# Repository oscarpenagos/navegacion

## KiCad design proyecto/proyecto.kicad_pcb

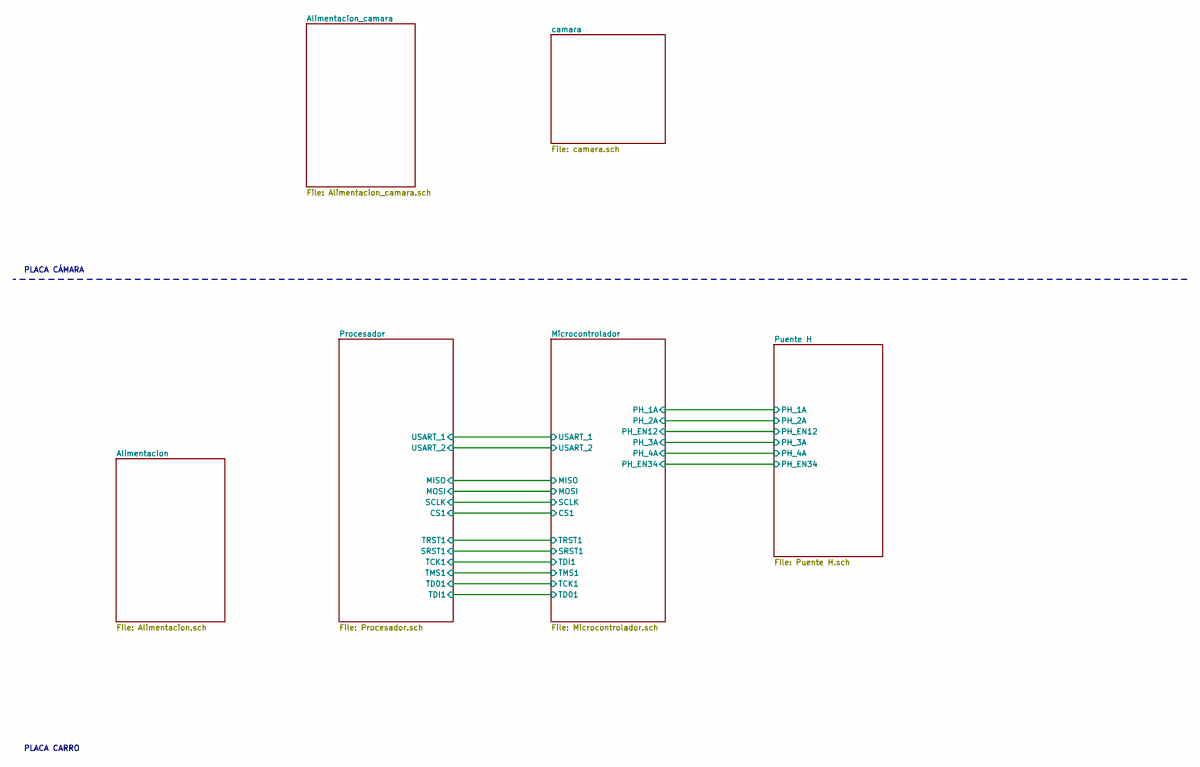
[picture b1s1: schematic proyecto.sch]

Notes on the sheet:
PLACA CÁMARA
PLACA CARRO

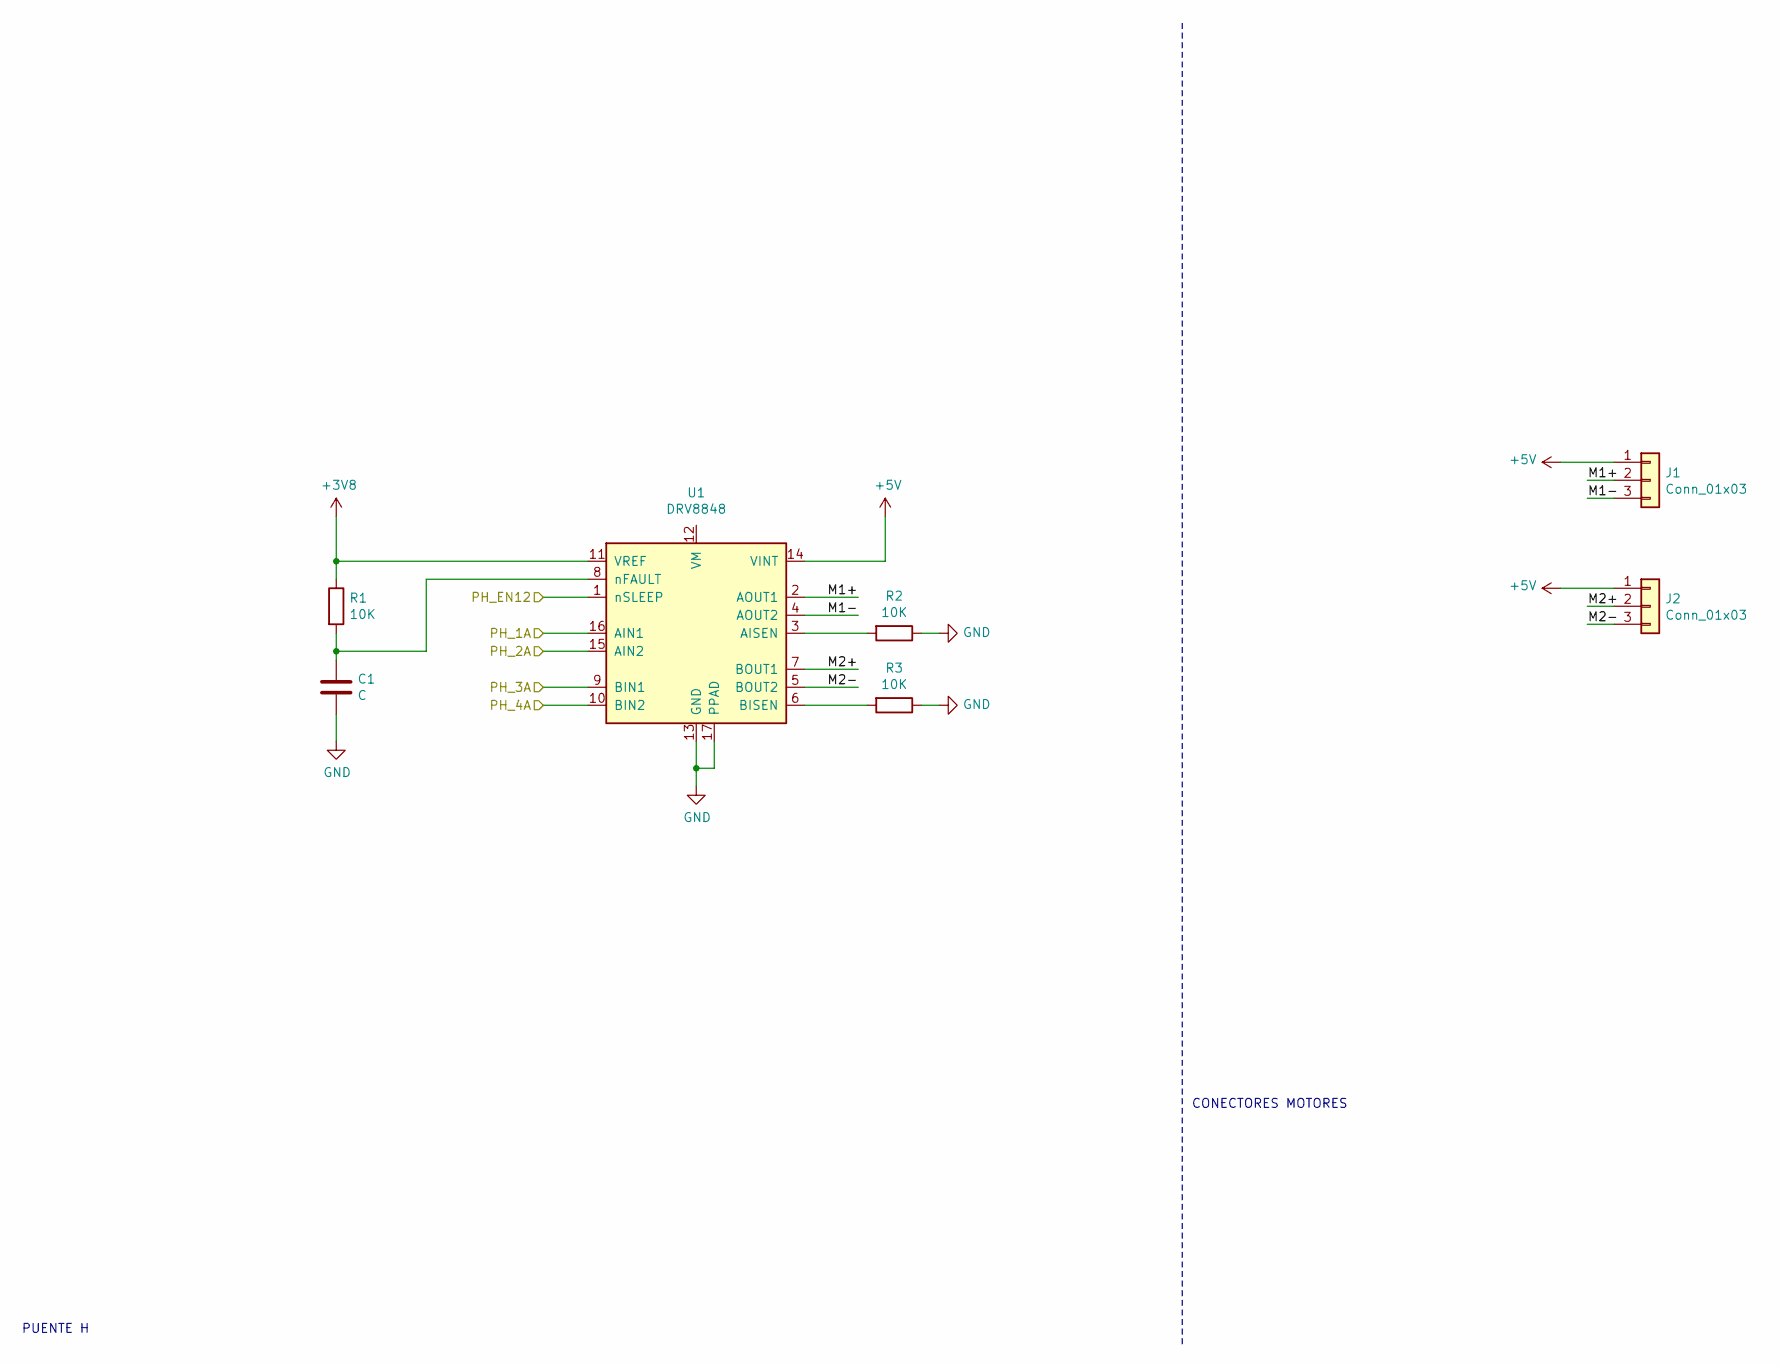
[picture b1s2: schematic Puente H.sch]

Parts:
C1: C; C_0603_1608Metric_Pad1.05x0.95mm_HandSolder
J1, J2: Conn_01x03; JST_EH_B3B-EH-A_1x03_P2.50mm_Vertical
R1, R2, R3: 10K; R_0201_0603Metric
U1: DRV8848; TSSOP-16-1EP_4.4x5mm_P0.65mm

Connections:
+3V8: R1.1, U1.11 (VREF); also elsewhere on the board
+5V: J1.1, J2.1, U1.14 (VINT); also elsewhere on the board
/Microcontrolador/PH_1A: U1.16 (AIN1); also elsewhere on the board
/Microcontrolador/PH_2A: U1.15 (AIN2); also elsewhere on the board
/Microcontrolador/PH_3A: U1.9 (BIN1); also elsewhere on the board
/Microcontrolador/PH_4A: U1.10 (BIN2); also elsewhere on the board
/Microcontrolador/PH_EN12: U1.1 (nSLEEP); also elsewhere on the board
/Puente H/M1+: J1.2, U1.2 (AOUT1)
/Puente H/M1-: J1.3, U1.4 (AOUT2)
/Puente H/M2+: J2.2, U1.7 (BOUT1)
/Puente H/M2-: J2.3, U1.5 (BOUT2)
GND: C1.2, R2.1, R3.1, U1.13 (GND), U1.17 (PPAD); also elsewhere on the board
unnamed: C1.1, R1.2, U1.8 (nFAULT)
unnamed: R2.2, U1.3 (AISEN)
unnamed: R3.2, U1.6 (BISEN)

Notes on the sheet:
CONECTORES MOTORES
PUENTE H

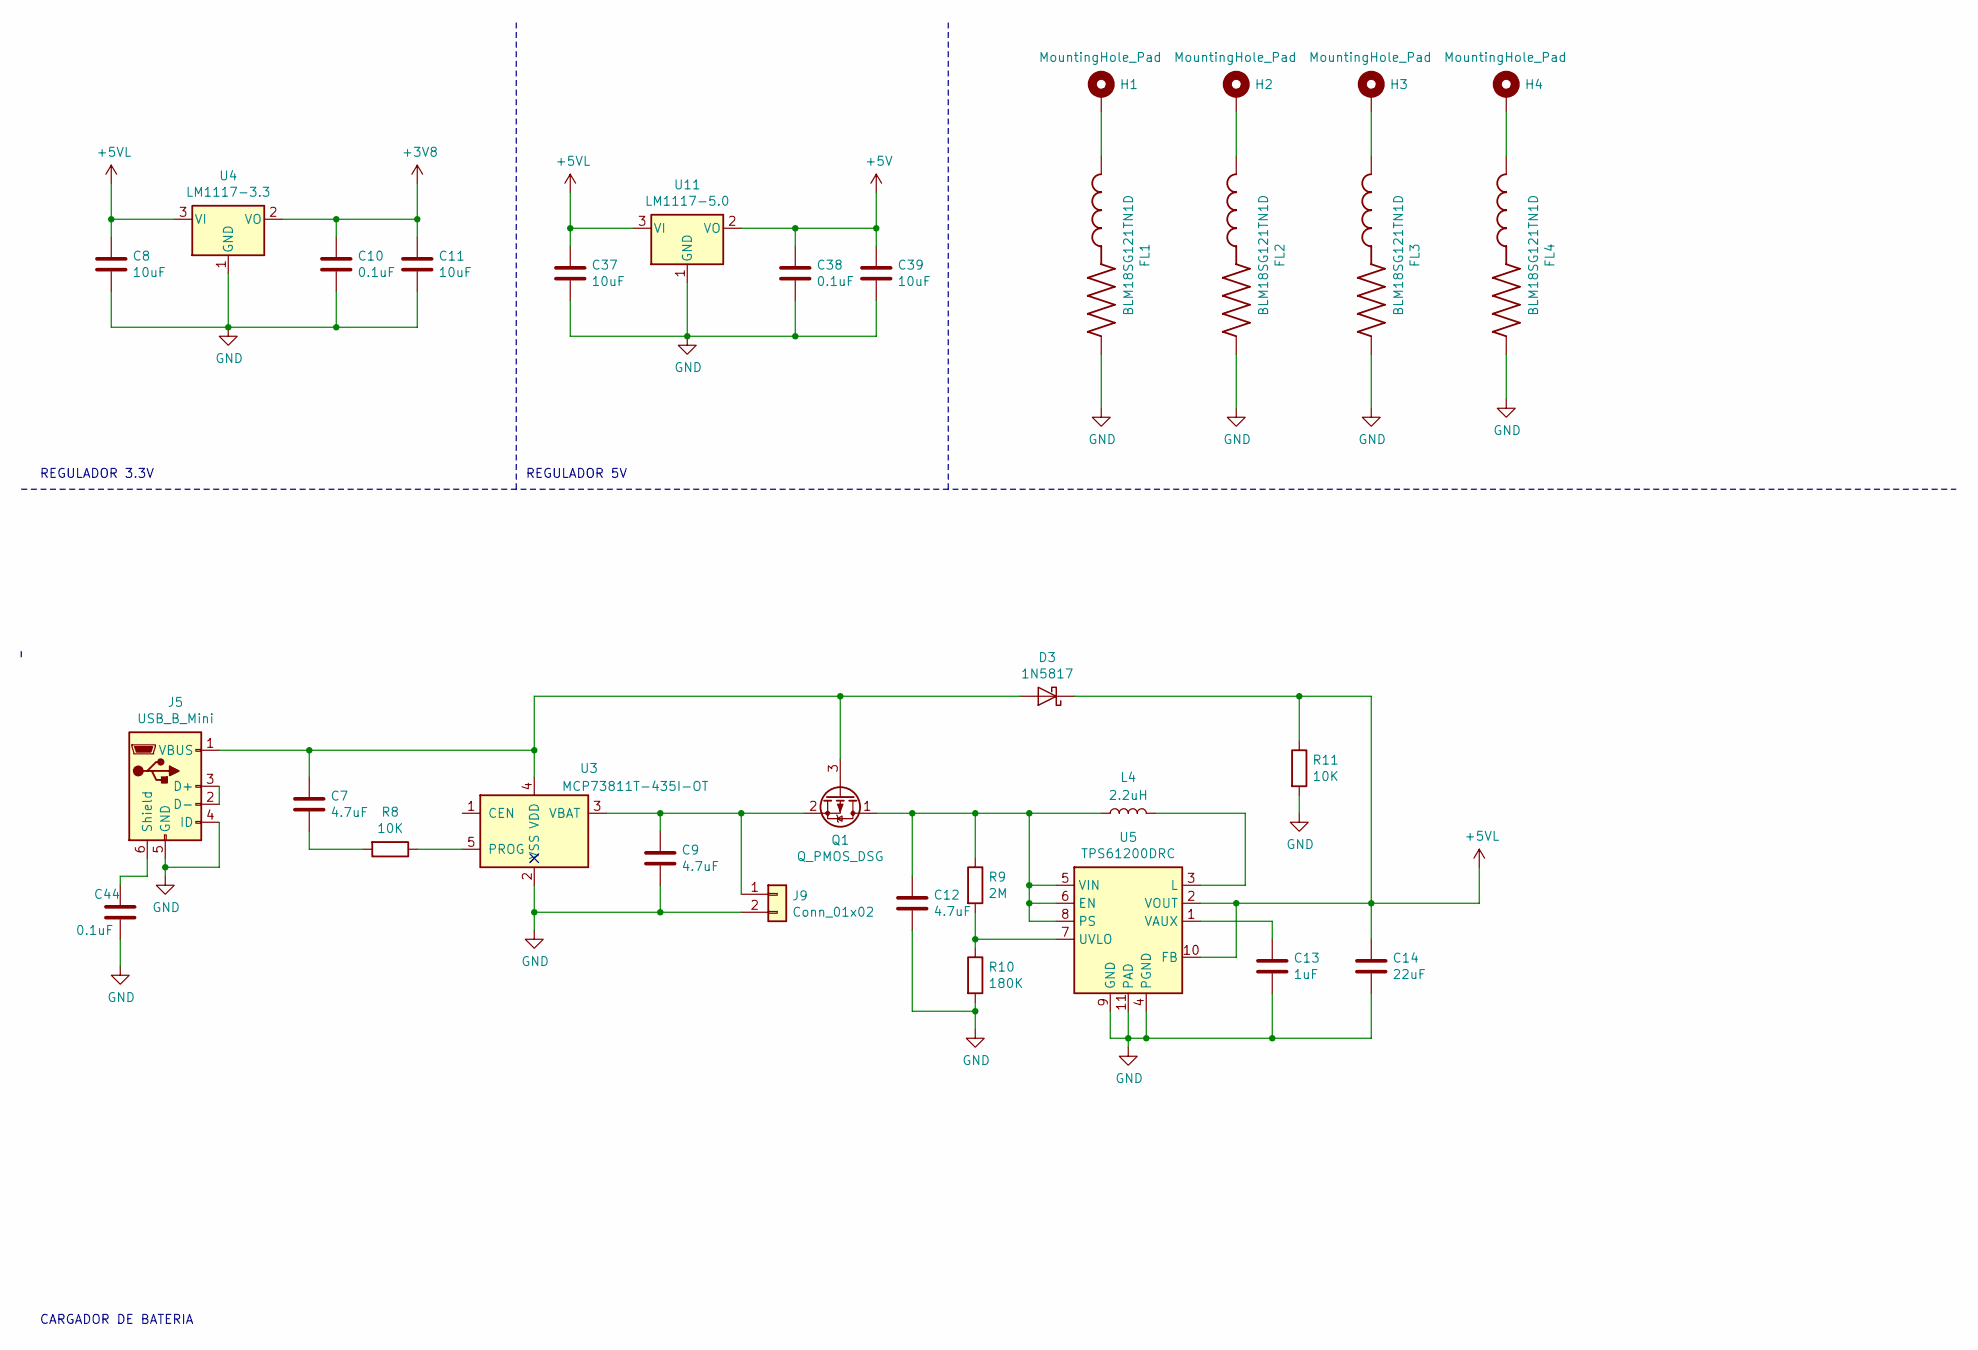
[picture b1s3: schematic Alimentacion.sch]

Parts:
C7, C9, C12: 4.7uF; C_0603_1608Metric_Pad1.05x0.95mm_HandSolder
C8, C11, C37, C39: 10uF; C_0603_1608Metric_Pad1.05x0.95mm_HandSolder
C10, C38, C44: 0.1uF; C_0603_1608Metric_Pad1.05x0.95mm_HandSolder
C13: 1uF; C_0603_1608Metric_Pad1.05x0.95mm_HandSolder
C14: 22uF; C_0603_1608Metric_Pad1.05x0.95mm_HandSolder
D3: 1N5817; D_DO-41_SOD81_P5.08mm_Vertical_AnodeUp
FL1, FL2, FL3, FL4: BLM18SG121TN1D; R_0603_1608Metric_Pad1.05x0.95mm_HandSolder
H1, H2, H3, H4: MountingHole_Pad; MountingHole_2.5mm_Pad
J5: USB_B_Mini; USB_Mini-B_AdamTech_MUSB-B5-S-VT-TSMT-1_SMD_Vertical
J9: Conn_01x02; PinHeader_1x02_P1.00mm_Horizontal
L4: 2.2uH; L_2010_5025Metric_Pad1.52x2.65mm_HandSolder
Q1: Q_PMOS_DSG; SOT-23
R8, R11: 10K; R_0603_1608Metric_Pad1.05x0.95mm_HandSolder
R9: 2M; R_0603_1608Metric_Pad1.05x0.95mm_HandSolder
R10: 180K; R_0603_1608Metric_Pad1.05x0.95mm_HandSolder
U3: MCP73811T-435I-OT; SOT-23-5
U4: LM1117-3.3; SOT-223
U5: TPS61200DRC; Texas_S-PVSON-N10_ThermalVias
U11: LM1117-5.0; SOT-223

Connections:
+3V8: C10.1, C11.1, U4.2 (VO); also elsewhere on the board
+5V: C38.1, C39.1, U11.2 (VO); also elsewhere on the board
+5VL: C8.1, C14.1, C37.1, D3.1 (K), R11.1, U4.3 (VI), U5.2 (VOUT), U5.10 (FB), U11.3 (VI)
GND: C8.2, C9.2, C10.2, C11.2, C12.2, C13.2, C14.2, C37.2, C38.2, C39.2, C44.2, FL1.2, FL2.2, FL3.2, FL4.2, J5.4 (ID), J5.5 (GND), J9.2, R10.2, R11.2, U3.2 (VSS), U4.1 (GND), U5.4 (PGND), U5.9 (GND), U5.11 (PAD), U11.1 (GND); also elsewhere on the board
unnamed: C7.1, D3.2 (A), J5.1 (VBUS), Q1.3 (G), U3.4 (VDD)
unnamed: C7.2, R8.2
unnamed: C9.1, J9.1, Q1.2 (S), U3.3 (VBAT)
unnamed: C12.1, L4.1, Q1.1 (D), R9.1, U5.5 (VIN), U5.6 (EN), U5.8 (PS)
unnamed: C13.1, U5.1 (VAUX)
unnamed: C44.1, J5.6 (Shield)
unnamed: FL1.1, H1.1
unnamed: FL2.1, H2.1
unnamed: FL3.1, H3.1
unnamed: FL4.1, H4.1
unnamed: J5.2 (D-), J5.3 (D+)
unnamed: L4.2, U5.3 (L)
unnamed: R8.1, U3.5 (PROG)
unnamed: R9.2, R10.1, U5.7 (UVLO)

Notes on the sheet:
CARGADOR DE BATERIA
REGULADOR 3.3V
REGULADOR 5V

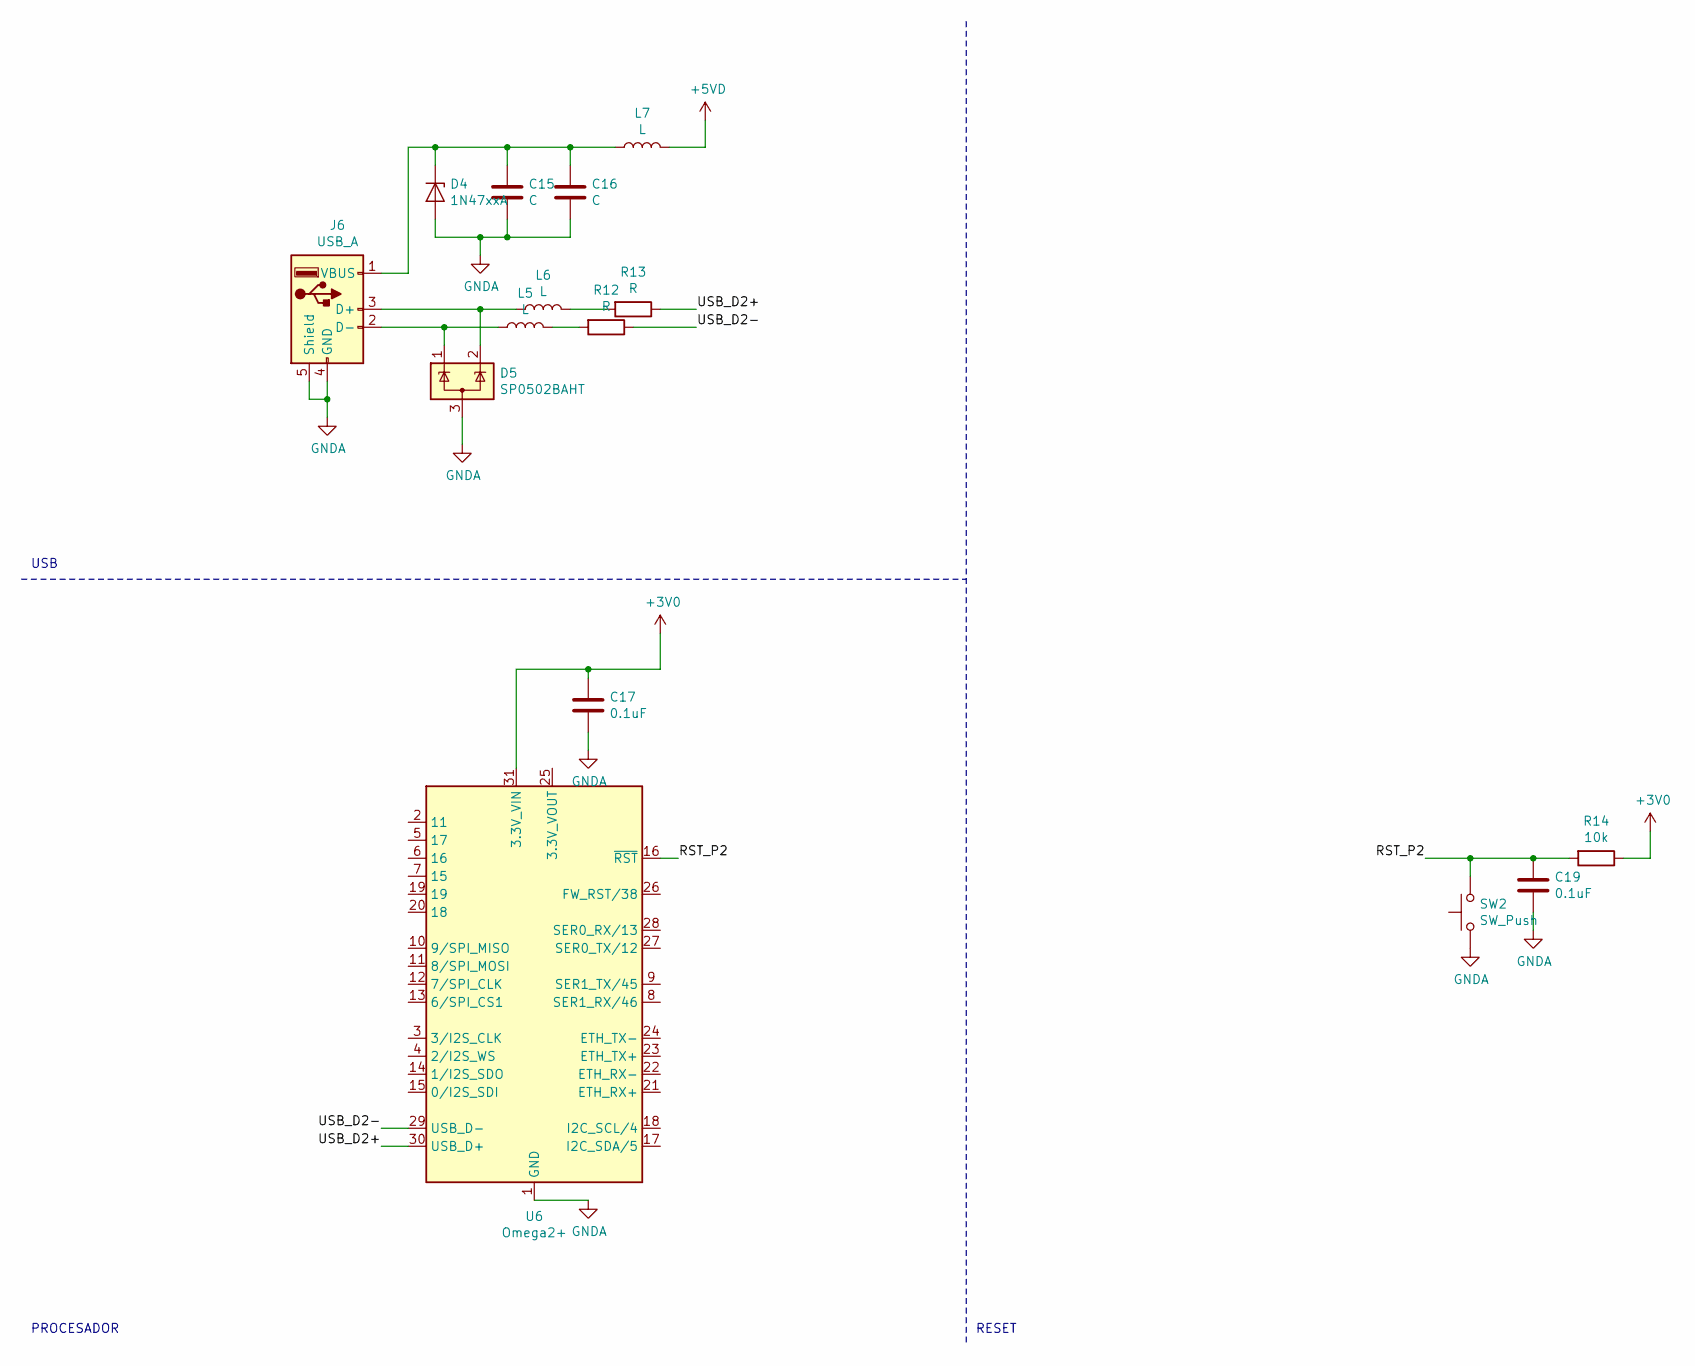
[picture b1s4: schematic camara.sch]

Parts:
C15, C16: C; C_0603_1608Metric_Pad1.05x0.95mm_HandSolder
C17, C19: 0.1uF; C_0603_1608Metric_Pad1.05x0.95mm_HandSolder
D4: 1N47xxA; D_DO-41_SOD81_P5.08mm_Vertical_AnodeUp
D5: SP0502BAHT; SOT-23
J6: USB_A; USB_A_Molex_105057_Vertical
L5, L6, L7: L; L_2010_5025Metric_Pad1.52x2.65mm_HandSolder
R12, R13: R; R_0603_1608Metric_Pad1.05x0.95mm_HandSolder
R14: 10k; R_0603_1608Metric_Pad1.05x0.95mm_HandSolder
SW2: SW_Push; SW_Push_1P1T_NO_6x6mm_H9.5mm
U6: Omega2+; Onion_Omega2+

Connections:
+3V0: C17.1, R14.1, U6.31 (3.3V_VIN); also elsewhere on the board
+5VD: L7.2; also elsewhere on the board
/camara/RST_P2: C19.1, R14.2, SW2.2, U6.16 (~RST)
/camara/USB_D2+: R13.1, U6.30 (USB_D+)
/camara/USB_D2-: R12.1, U6.29 (USB_D-)
GNDA: C15.2, C16.2, C17.2, C19.2, D4.2 (A), D5.3 (A), J6.4 (GND), J6.5 (Shield), SW2.1, U6.1 (GND), U6.32 (GND); also elsewhere on the board
unnamed: C15.1, C16.1, D4.1 (K), J6.1 (VBUS), L7.1
unnamed: D5.1 (K), J6.2 (D-), L5.1
unnamed: D5.2 (K), J6.3 (D+), L6.1
unnamed: L5.2, R12.2
unnamed: L6.2, R13.2

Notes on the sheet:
RESET
PROCESADOR
USB

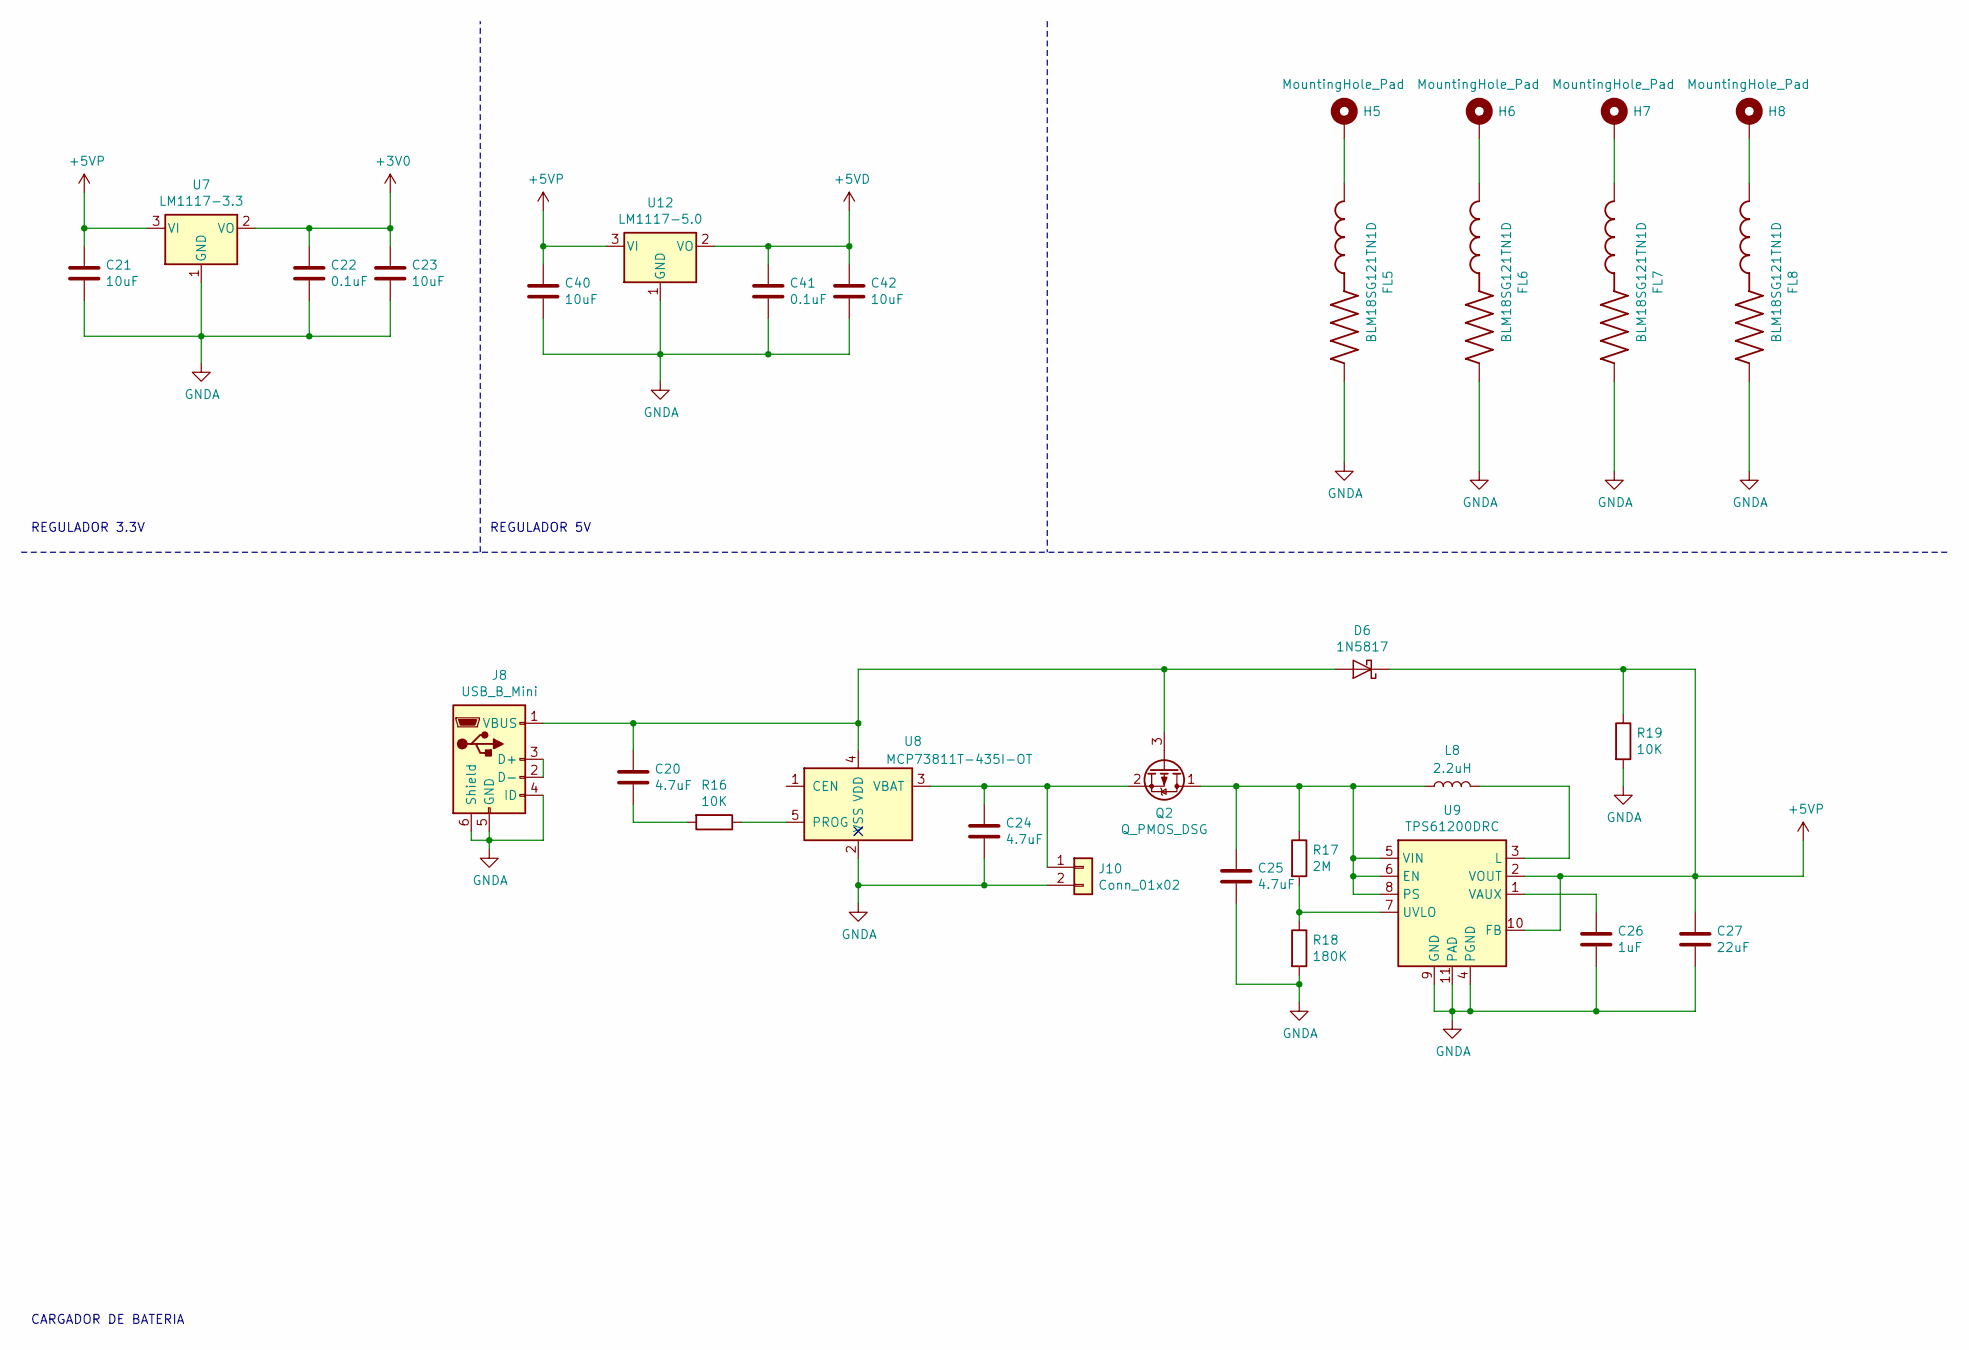
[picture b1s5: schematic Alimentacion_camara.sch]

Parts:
C20, C24, C25: 4.7uF; C_0603_1608Metric_Pad1.05x0.95mm_HandSolder
C21, C23, C40, C42: 10uF; C_0603_1608Metric_Pad1.05x0.95mm_HandSolder
C22, C41: 0.1uF; C_0603_1608Metric_Pad1.05x0.95mm_HandSolder
C26: 1uF; C_0603_1608Metric_Pad1.05x0.95mm_HandSolder
C27: 22uF; C_0603_1608Metric_Pad1.05x0.95mm_HandSolder
D6: 1N5817; D_DO-41_SOD81_P10.16mm_Horizontal
FL5, FL6, FL7, FL8: BLM18SG121TN1D; R_0603_1608Metric_Pad1.05x0.95mm_HandSolder
H5, H6, H7, H8: MountingHole_Pad; MountingHole_2.5mm_Pad
J8: USB_B_Mini; USB_Mini-B_AdamTech_MUSB-B5-S-VT-TSMT-1_SMD_Vertical
J10: Conn_01x02; PinHeader_1x02_P1.00mm_Horizontal
L8: 2.2uH; L_2010_5025Metric_Pad1.52x2.65mm_HandSolder
Q2: Q_PMOS_DSG; SOT-23
R16, R19: 10K; R_0603_1608Metric_Pad1.05x0.95mm_HandSolder
R17: 2M; R_0603_1608Metric_Pad1.05x0.95mm_HandSolder
R18: 180K; R_0603_1608Metric_Pad1.05x0.95mm_HandSolder
U7: LM1117-3.3; SOT-223
U8: MCP73811T-435I-OT; SOT-23-5
U9: TPS61200DRC; Texas_S-PVSON-N10_ThermalVias
U12: LM1117-5.0; SOT-223

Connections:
+3V0: C22.1, C23.1, U7.2 (VO); also elsewhere on the board
+5VD: C41.1, C42.1, U12.2 (VO); also elsewhere on the board
+5VP: C21.1, C27.1, C40.1, D6.1 (K), R19.1, U7.3 (VI), U9.2 (VOUT), U9.10 (FB), U12.3 (VI)
GNDA: C21.2, C22.2, C23.2, C24.2, C25.2, C26.2, C27.2, C40.2, C41.2, C42.2, FL5.2, FL6.2, FL7.2, FL8.2, J8.4 (ID), J8.5 (GND), J8.6 (Shield), J10.2, R18.2, R19.2, U7.1 (GND), U8.2 (VSS), U9.4 (PGND), U9.9 (GND), U9.11 (PAD), U12.1 (GND); also elsewhere on the board
unnamed: C20.1, D6.2 (A), J8.1 (VBUS), Q2.3 (G), U8.4 (VDD)
unnamed: C20.2, R16.2
unnamed: C24.1, J10.1, Q2.2 (S), U8.3 (VBAT)
unnamed: C25.1, L8.1, Q2.1 (D), R17.1, U9.5 (VIN), U9.6 (EN), U9.8 (PS)
unnamed: C26.1, U9.1 (VAUX)
unnamed: FL5.1, H5.1
unnamed: FL6.1, H6.1
unnamed: FL7.1, H7.1
unnamed: FL8.1, H8.1
unnamed: J8.2 (D-), J8.3 (D+)
unnamed: L8.2, U9.3 (L)
unnamed: R16.1, U8.5 (PROG)
unnamed: R17.2, R18.1, U9.7 (UVLO)

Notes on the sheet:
REGULADOR 3.3V
CARGADOR DE BATERIA
REGULADOR 5V

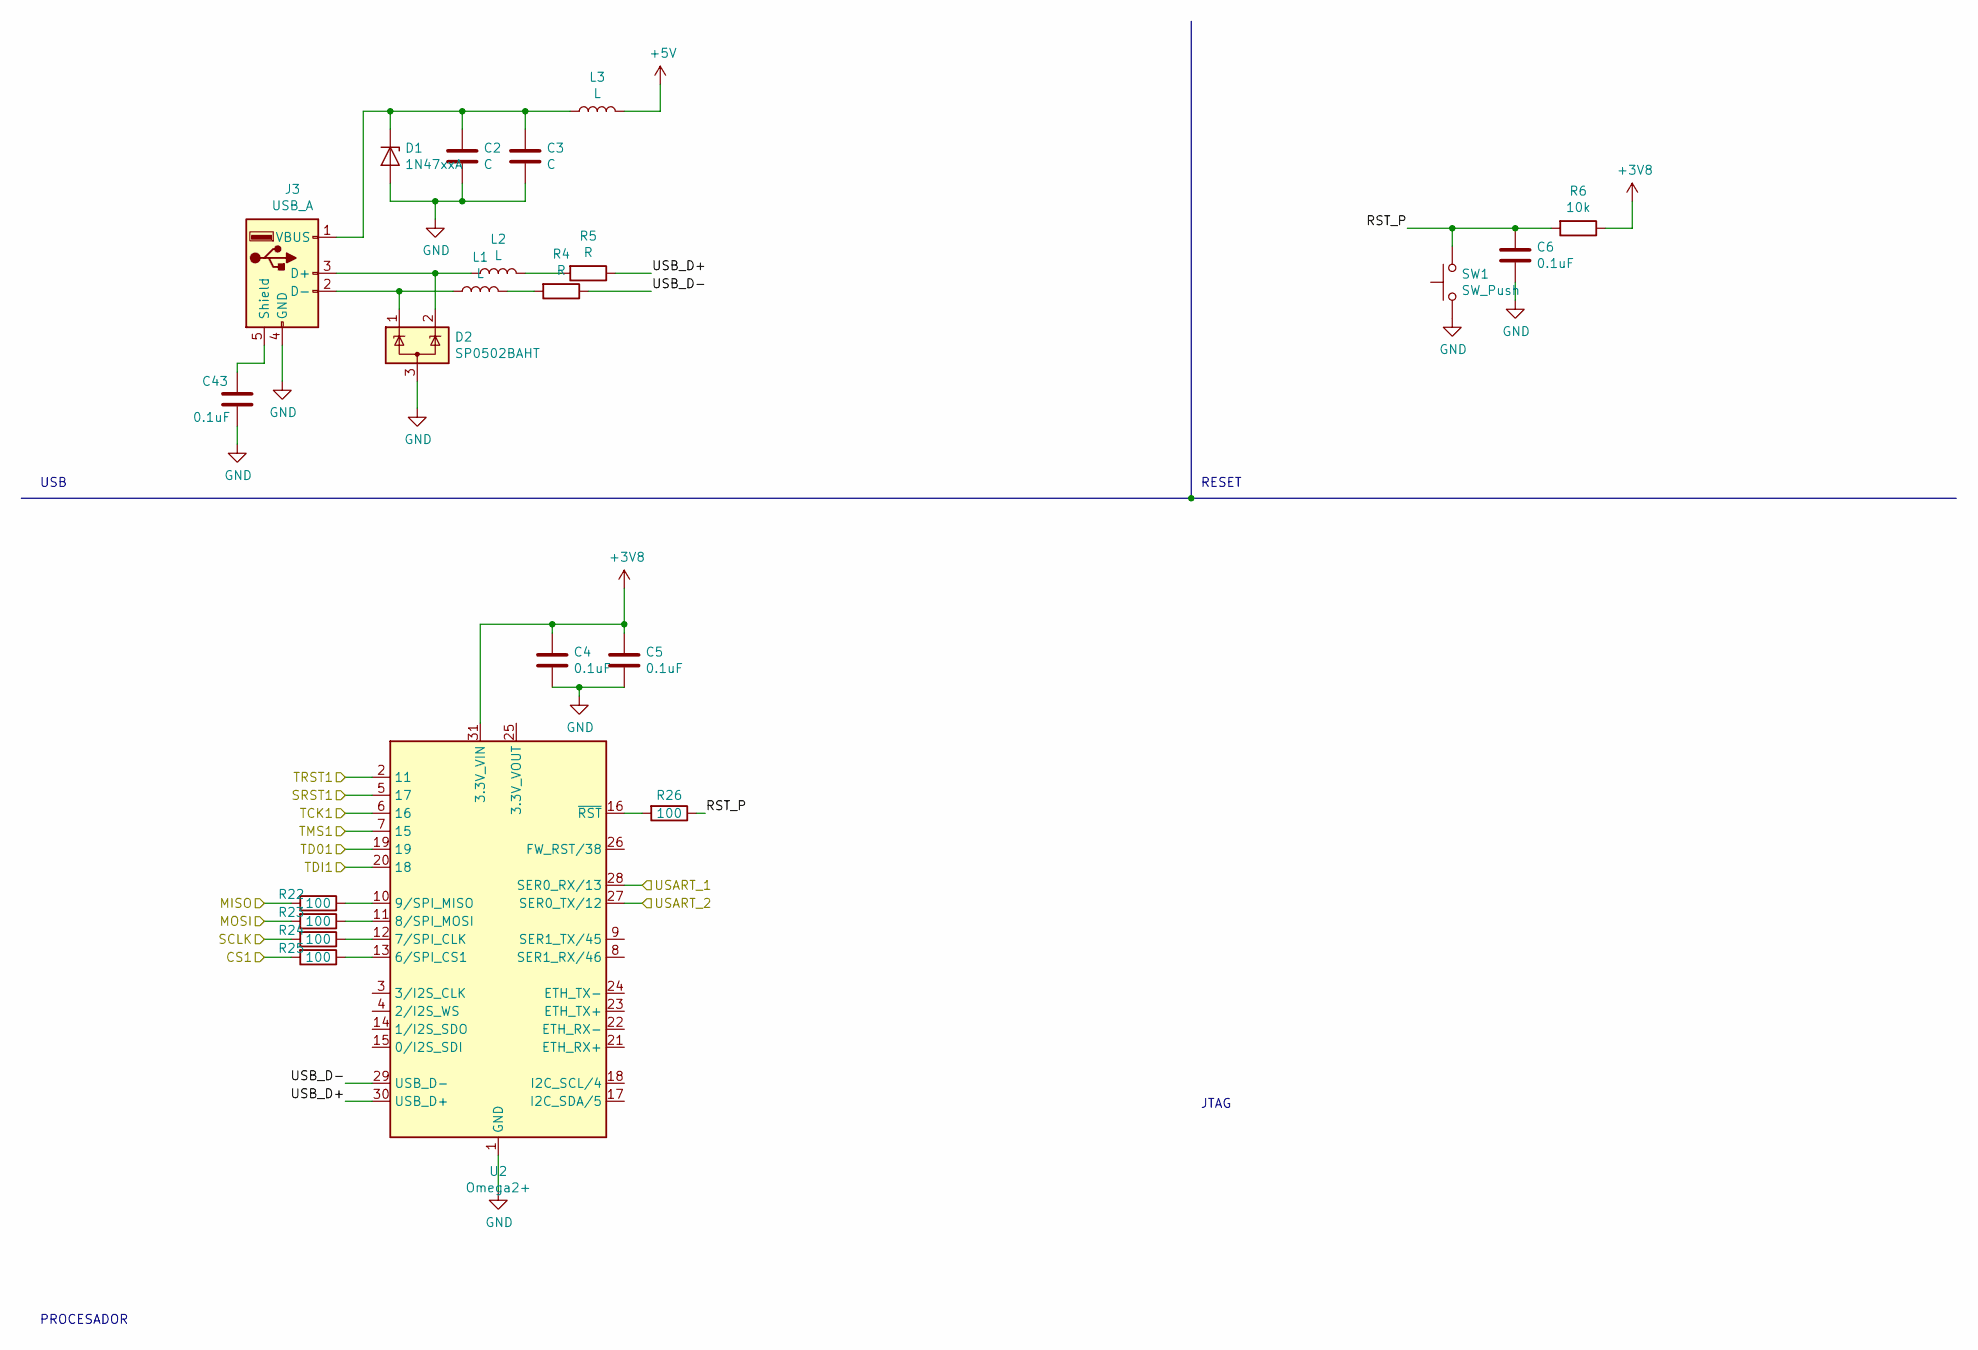
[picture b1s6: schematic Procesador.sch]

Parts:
C2, C3: C; C_0603_1608Metric_Pad1.05x0.95mm_HandSolder
C4, C5, C6, C43: 0.1uF; C_0603_1608Metric_Pad1.05x0.95mm_HandSolder
D1: 1N47xxA; D_DO-41_SOD81_P5.08mm_Vertical_AnodeUp
D2: SP0502BAHT; SOT-23
J3: USB_A; USB_A_Molex_105057_Vertical
L1, L2, L3: L; L_2010_5025Metric_Pad1.52x2.65mm_HandSolder
R4, R5: R; R_0603_1608Metric_Pad1.05x0.95mm_HandSolder
R6: 10k; R_0603_1608Metric_Pad1.05x0.95mm_HandSolder
R22, R23, R24, R25, R26: 100; R_0603_1608Metric_Pad1.05x0.95mm_HandSolder
SW1: SW_Push; SW_Push_1P1T_NO_6x6mm_H9.5mm
U2: Omega2+; Onion_Omega2+

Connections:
+3V8: C4.1, C5.1, R6.1, U2.31 (3.3V_VIN); also elsewhere on the board
+5V: L3.2; also elsewhere on the board
/Microcontrolador/CS1: R25.2; also elsewhere on the board
/Microcontrolador/MISO: R22.2; also elsewhere on the board
/Microcontrolador/MOSI: R23.2; also elsewhere on the board
/Microcontrolador/SCLK: R24.2; also elsewhere on the board
/Microcontrolador/SRST1: U2.5 (17); also elsewhere on the board
/Microcontrolador/TCK1: U2.19; also elsewhere on the board
/Microcontrolador/TD01: U2.20 (18); also elsewhere on the board
/Microcontrolador/TMS1: U2.7 (15); also elsewhere on the board
/Microcontrolador/TRST1: U2.2 (11); also elsewhere on the board
/Microcontrolador/USART_1: U2.28 (SER0_RX/13); also elsewhere on the board
/Microcontrolador/USART_2: U2.27 (SER0_TX/12); also elsewhere on the board
/Procesador/RST_P: C6.1, R6.2, R26.1, SW1.2
/Procesador/TCK1: U2.6 (16); also elsewhere on the board
/Procesador/USB_D+: R5.1, U2.30 (USB_D+)
/Procesador/USB_D-: R4.1, U2.29 (USB_D-)
GND: C2.2, C3.2, C4.2, C5.2, C6.2, C43.2, D1.2 (A), D2.3 (A), J3.4 (GND), SW1.1, U2.1 (GND), U2.32 (GND); also elsewhere on the board
unnamed: C2.1, C3.1, D1.1 (K), J3.1 (VBUS), L3.1
unnamed: C43.1, J3.5 (Shield)
unnamed: D2.1 (K), J3.2 (D-), L1.1
unnamed: D2.2 (K), J3.3 (D+), L2.1
unnamed: L1.2, R4.2
unnamed: L2.2, R5.2
unnamed: R22.1, U2.10 (9/SPI_MISO)
unnamed: R23.1, U2.11 (8/SPI_MOSI)
unnamed: R24.1, U2.12 (7/SPI_CLK)
unnamed: R25.1, U2.13 (6/SPI_CS1)
unnamed: R26.2, U2.16 (~RST)

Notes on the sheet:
USB
PROCESADOR
JTAG
RESET

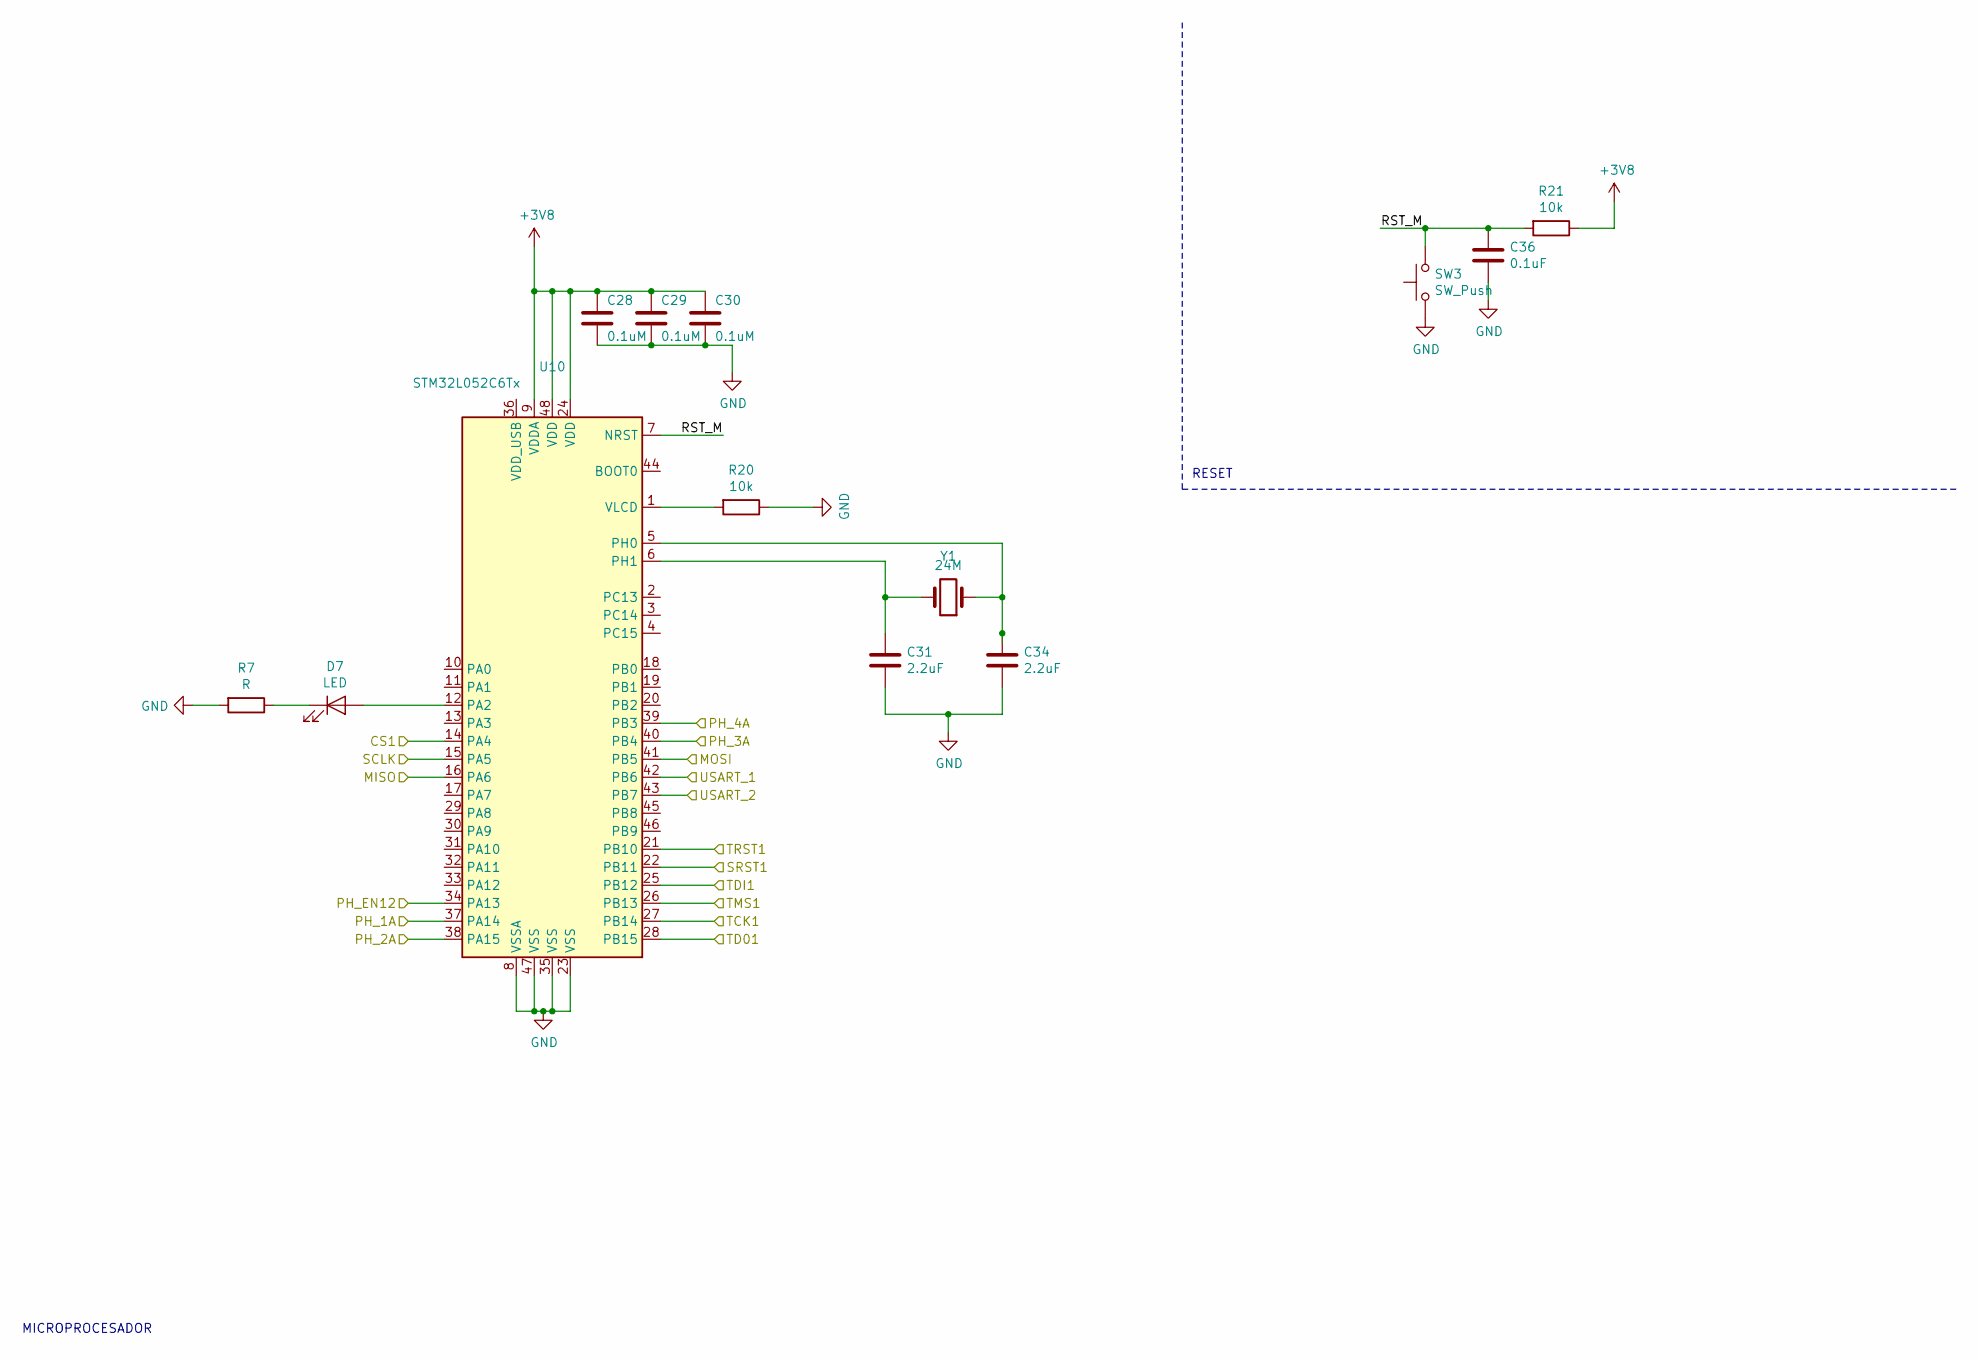
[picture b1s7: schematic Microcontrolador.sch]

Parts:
C28, C29, C30: 0.1uM; C_0603_1608Metric_Pad1.05x0.95mm_HandSolder
C31: 2.2uF; L_2010_5025Metric_Pad1.52x2.65mm_HandSolder
C34: 2.2uF; C_0603_1608Metric_Pad1.05x0.95mm_HandSolder
C36: 0.1uF; C_0603_1608Metric_Pad1.05x0.95mm_HandSolder
D7: LED; D_0805_2012Metric_Pad1.15x1.40mm_HandSolder
R7: R; R_0603_1608Metric_Pad1.05x0.95mm_HandSolder
R20, R21: 10k; R_0603_1608Metric_Pad1.05x0.95mm_HandSolder
SW3: SW_Push; SW_Push_1P1T_NO_6x6mm_H9.5mm
U10: STM32L052C6Tx; LQFP-48_7x7mm_P0.5mm
Y1: 24M; Crystal_HC49-U_Vertical

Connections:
+3V8: C28.1, C29.1, C30.1, R21.1, U10.9 (VDDA), U10.24 (VDD), U10.48 (VDD); also elsewhere on the board
/Microcontrolador/CS1: U10.14 (PA4); also elsewhere on the board
/Microcontrolador/MISO: U10.16 (PA6); also elsewhere on the board
/Microcontrolador/MOSI: U10.41 (PB5); also elsewhere on the board
/Microcontrolador/PH_1A: U10.37 (PA14); also elsewhere on the board
/Microcontrolador/PH_2A: U10.38 (PA15); also elsewhere on the board
/Microcontrolador/PH_3A: U10.40 (PB4); also elsewhere on the board
/Microcontrolador/PH_4A: U10.39 (PB3); also elsewhere on the board
/Microcontrolador/PH_EN12: U10.34 (PA13); also elsewhere on the board
/Microcontrolador/RST_M: C36.1, R21.2, SW3.2, U10.7 (NRST)
/Microcontrolador/SCLK: U10.15 (PA5); also elsewhere on the board
/Microcontrolador/SRST1: U10.22 (PB11); also elsewhere on the board
/Microcontrolador/TCK1: U10.27 (PB14); also elsewhere on the board
/Microcontrolador/TD01: U10.28 (PB15); also elsewhere on the board
/Microcontrolador/TMS1: U10.26 (PB13); also elsewhere on the board
/Microcontrolador/TRST1: U10.21 (PB10); also elsewhere on the board
/Microcontrolador/USART_1: U10.42 (PB6); also elsewhere on the board
/Microcontrolador/USART_2: U10.43 (PB7); also elsewhere on the board
/Procesador/TCK1: U10.25 (PB12); also elsewhere on the board
GND: C28.2, C29.2, C30.2, C31.1, C34.1, C36.2, R7.2, R20.1, SW3.1, U10.8 (VSSA), U10.23 (VSS), U10.35 (VSS), U10.47 (VSS); also elsewhere on the board
unnamed: C31.2, U10.6 (PH1), Y1.2
unnamed: C34.2, U10.5 (PH0), Y1.1
unnamed: D7.1 (K), R7.1
unnamed: D7.2 (A), U10.12 (PA2)
unnamed: R20.2, U10.1 (VLCD)

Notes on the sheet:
RESET
MICROPROCESADOR
